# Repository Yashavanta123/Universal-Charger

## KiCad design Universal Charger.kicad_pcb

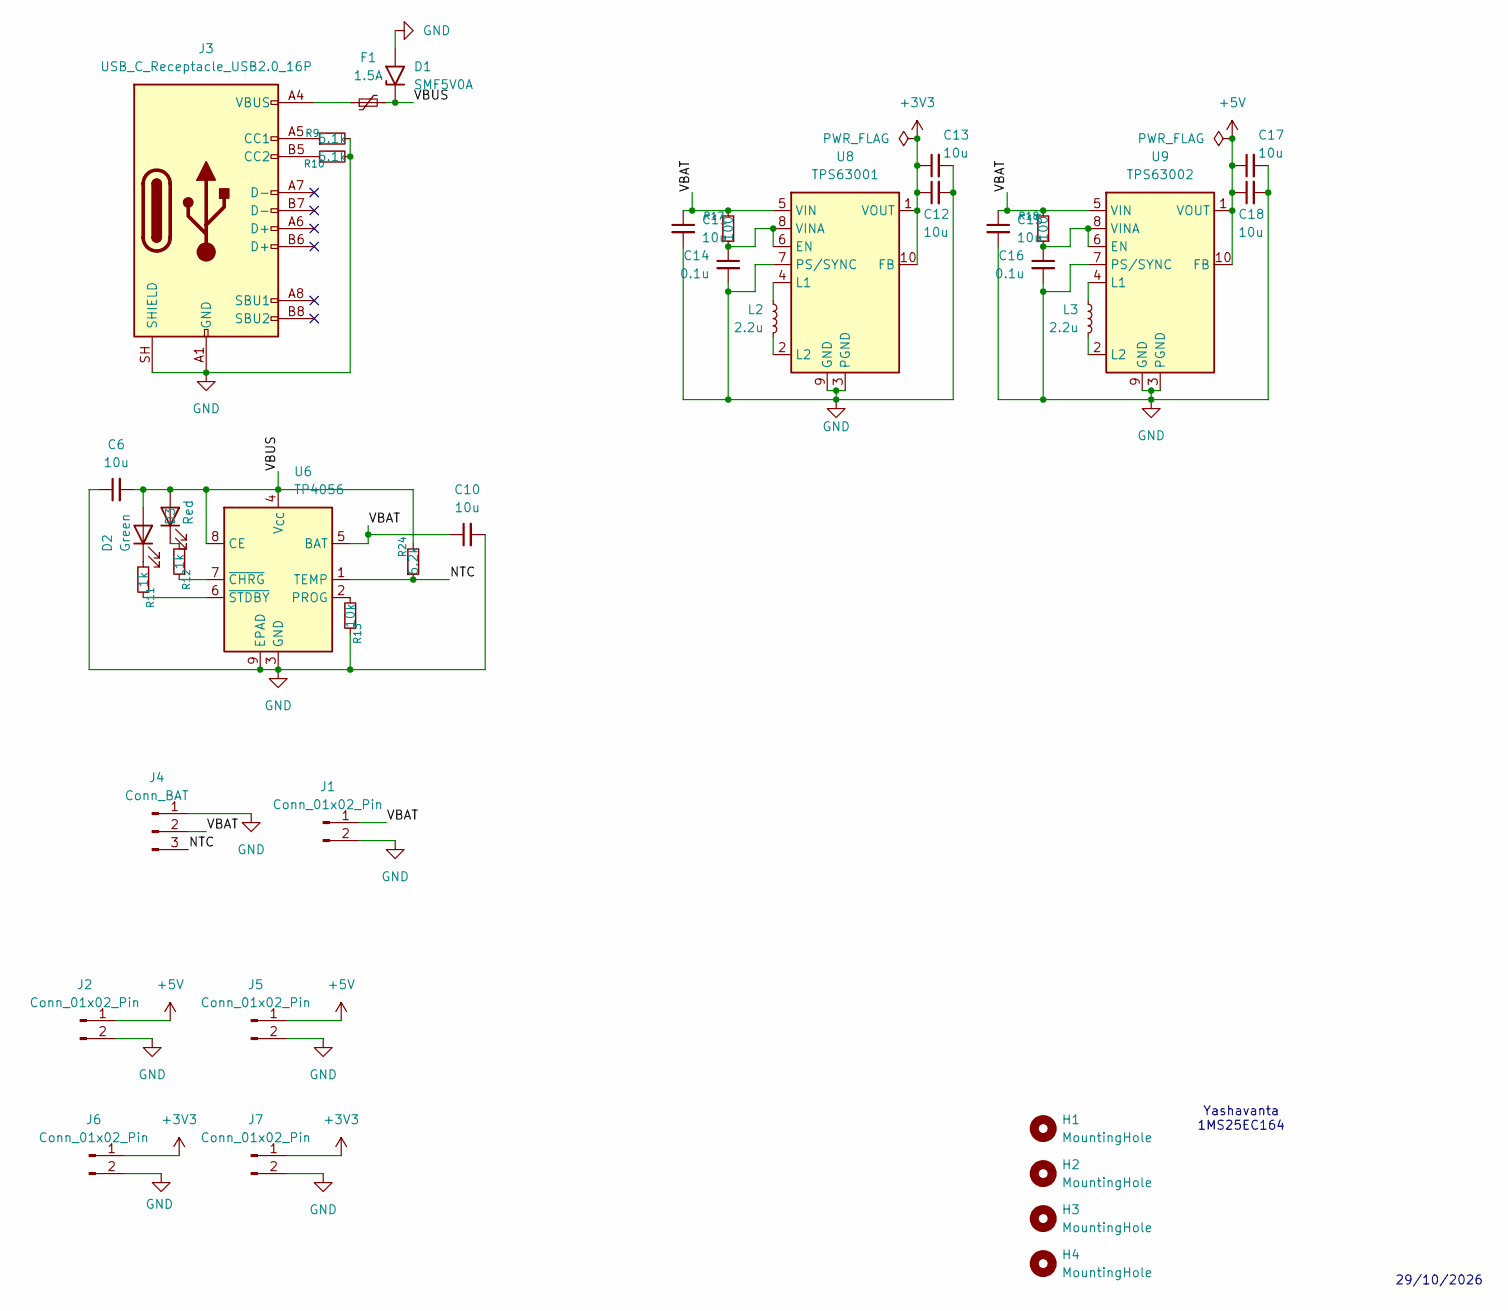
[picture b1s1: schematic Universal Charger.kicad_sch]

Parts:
C6, C10, C11, C12, C13, C15, C17, C18: 10u; C_0805_2012Metric
C14, C16: 0.1u; C_0603_1608Metric
D1: SMF5V0A; D_SMF
D2: Green; LED_0402_1005Metric
D3: Red; LED_0402_1005Metric
F1: 1.5A; Fuse_1206_3216Metric
H1, H2, H3, H4: MountingHole; MountingHole_2.7mm_M2.5
J1, J2: Conn_01x02_Pin; PinHeader_1x02_P2.54mm_Vertical
J3: USB_C_Receptacle_USB2.0_16P; USB_C_Receptacle_HRO_TYPE-C-31-M-12
J4: Conn_BAT; PinHeader_1x03_P1.27mm_Vertical
J5, J6, J7: Conn_01x02_Pin; PinHeader_1x02_P1.27mm_Vertical
L2, L3: 2.2u; L_1210_3225Metric
R9, R10: 5.1k; R_0201_0603Metric
R11, R12: 1k; R_0201_0603Metric
R13: 10k; R_0201_0603Metric
R17, R18: 100; R_0201_0603Metric
R24: 6.2k; R_0201_0603Metric
U6: TP4056; SOIC-8-1EP_3.9x4.9mm_P1.27mm_EP2.41x3.3mm_ThermalVias
U8: TPS63001; Texas_DRC0010J_ThermalVias
U9: TPS63002; Texas_DRC0010J_ThermalVias

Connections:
+3V3: C12.1, C13.1, J6.1, J7.1, U8.1 (VOUT), U8.10 (FB)
+5V: C17.1, C18.1, J2.1, J5.1, U9.1 (VOUT), U9.10 (FB)
/NTC: J4.3, R24.1, U6.1 (TEMP)
/VBAT: C10.1, C11.1, C15.1, J1.1, J4.2, R17.2, R18.2, U6.5 (BAT), U8.5 (VIN), U9.5 (VIN)
/VBUS: C6.2, D1.1 (A1), D2.2 (A), D3.2 (A), F1.2, R24.2, U6.4 (V_{CC}), U6.8 (CE)
GND: C6.1, C10.2, C11.2, C12.2, C13.2, C14.2, C15.2, C16.2, C17.2, C18.2, D1.2 (A2), J1.2, J2.2, J3.A1 (GND), J3.A12 (GND), J3.B1 (GND), J3.B12 (GND), J3.SH (SHIELD), J4.1, J5.2, J6.2, J7.2, R9.2, R10.2, R13.1, U6.3 (GND), U6.9 (EPAD), U8.3 (PGND), U8.7 (PS/SYNC), U8.9 (GND), U8.11 (PGND), U9.3 (PGND), U9.7 (PS/SYNC), U9.9 (GND), U9.11 (PGND)
unnamed: D2.1 (K), R11.2
unnamed: D3.1 (K), R12.2
unnamed: F1.1, J3.A4 (VBUS), J3.A9 (VBUS), J3.B4 (VBUS), J3.B9 (VBUS)
unnamed: J3.A5 (CC1), R9.1
unnamed: J3.B5 (CC2), R10.1
unnamed: R13.2, U6.2 (PROG)
unnamed: R12.1, U6.7 (~CHRG)
unnamed: R11.1, U6.6 (~STDBY)
unnamed: C14.1, R17.1, U8.6 (EN), U8.8 (VINA)
unnamed: L2.2, U8.4 (L1)
unnamed: L2.1, U8.2 (L2)
unnamed: C16.1, R18.1, U9.6 (EN), U9.8 (VINA)
unnamed: L3.2, U9.4 (L1)
unnamed: L3.1, U9.2 (L2)

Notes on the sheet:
Yashavanta 1MS25EC164
29/10/2026

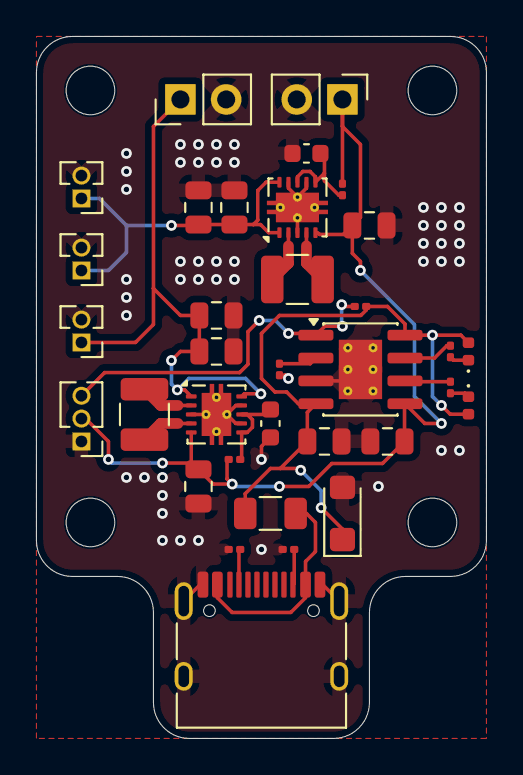
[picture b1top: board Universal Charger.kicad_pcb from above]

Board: 2 copper layers, 25.0 x 39.0 mm, 38 parts (0 on the bottom side), 20 nets.
